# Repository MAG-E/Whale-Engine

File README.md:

# Whale-Engine
CMOS based optical drone synthesiser

Youtube video: https://youtu.be/fdHDt4L-P9A

Everything you need to build one of these is included. This is not a 'true' beginner project, some mechanical and electrical skills are required.
Some assumptions will need to be made with drilling and wiring the output jack and power input jack.
The PCB files are formatted for JLC manufacture. The original PCB was hand etched so the schematic includes jumpers. These can be ignored if you
order a PCB.

The finished device draws 50mA at most, making it suitable for battery or USB power. Do not connect more than 9V, the zener diode regulation is very crude.
The output is not suitable for powering headphones and benefits from being connected to an amplifier. It is designed to be connected to an amplified speaker.

Known issues:
- Even with modulation switches set to off, the modulations oscillators have an effect on the primary oscillator.
  This could be fixed by using a separate 4093 IC for the modulation oscillators. In one unit, I isolated the LEDs with
  a transistor and the issue was still there. 
  The problem is only with a TI CD4093, the now obsolete OnSemi CD4093s I have do not exhibit this.
  This isn't a refined product, it was built for kids christmas presents.
  
MAG-03/01/2022

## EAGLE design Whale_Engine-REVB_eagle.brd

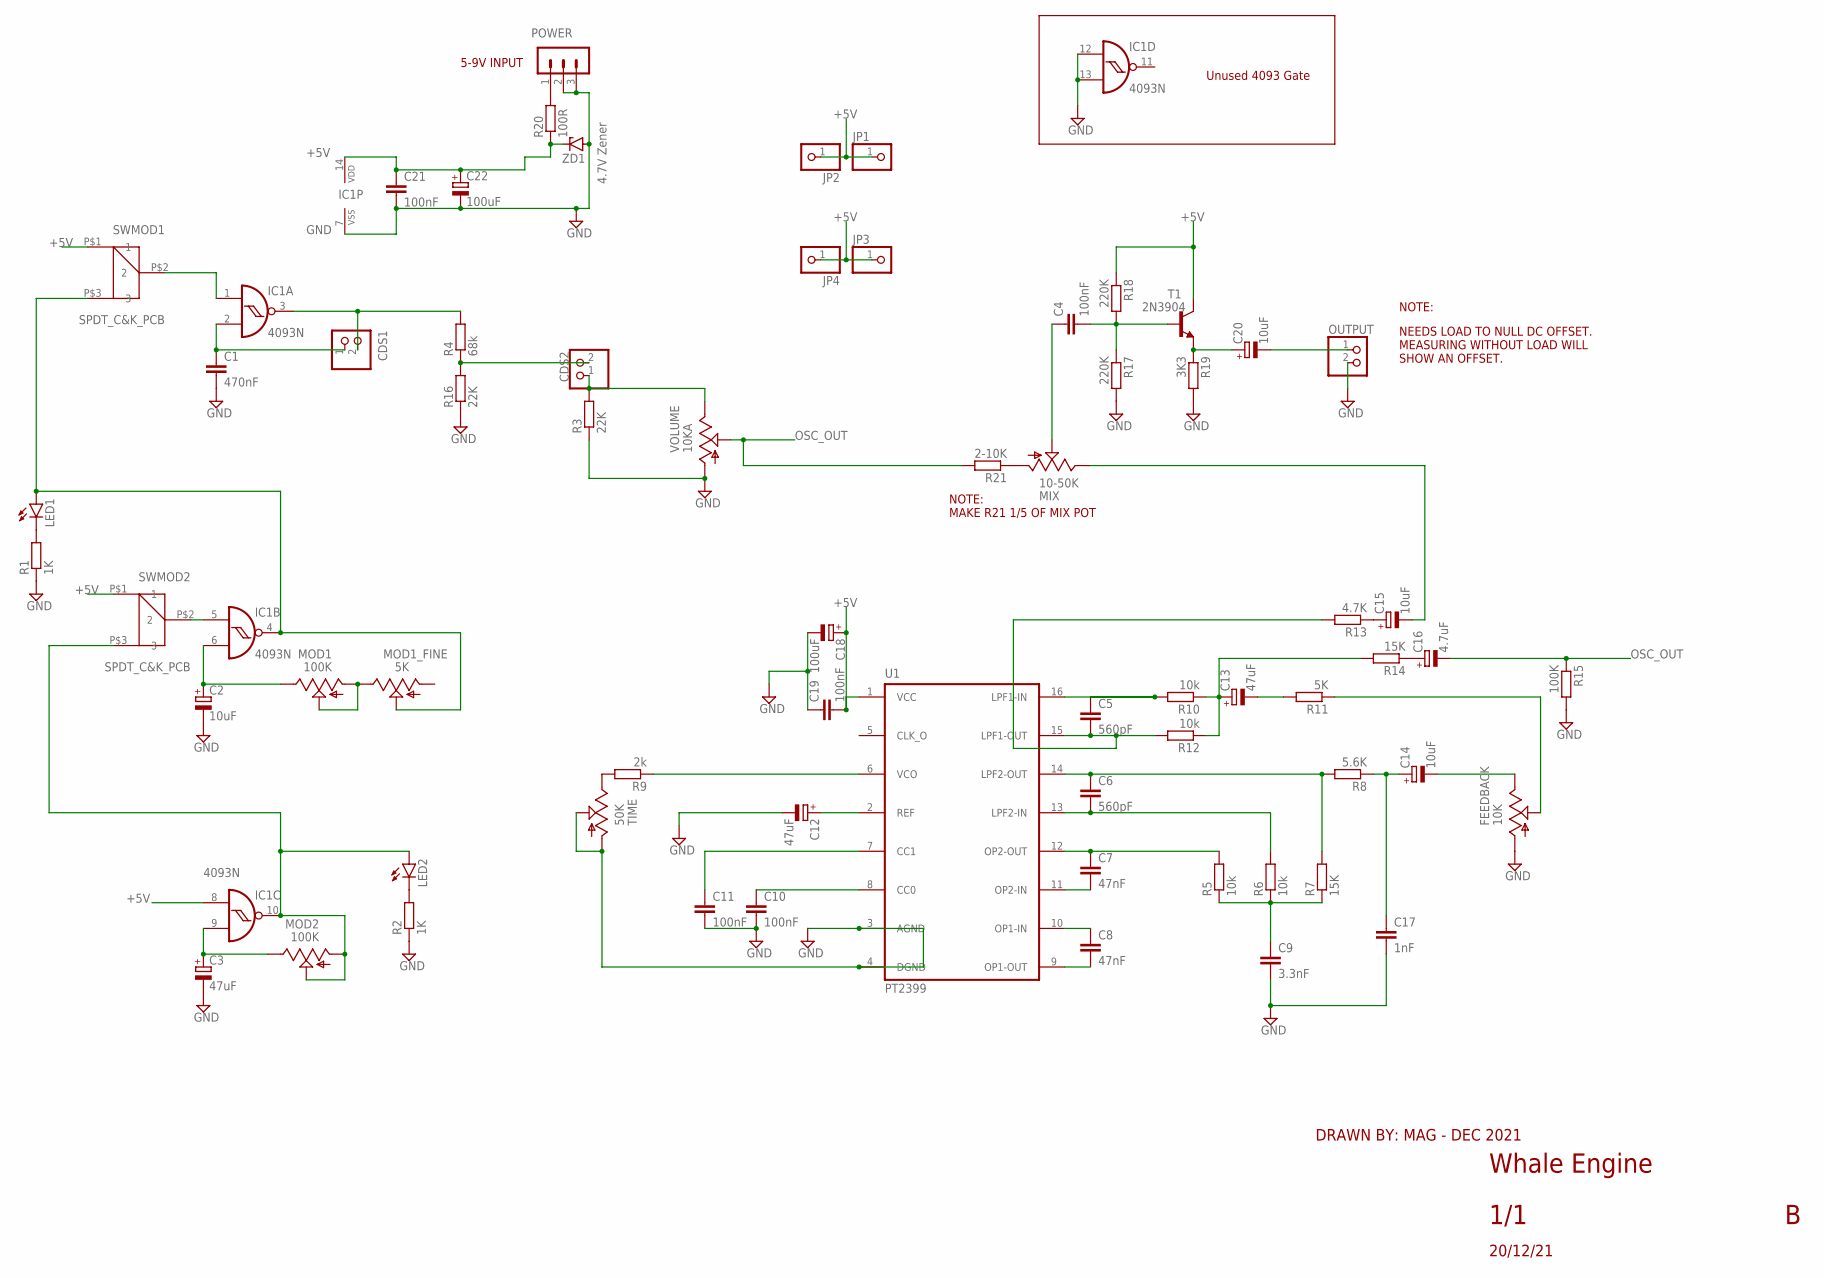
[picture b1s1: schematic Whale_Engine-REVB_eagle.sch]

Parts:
C1: 470nF; C7.5B3
C2, C14, C15, C20: 10uF; E2-5
C3, C12, C13: 47uF; E2-5
C4: 100nF; C050-025X075
C5, C6: 560pF; C2.5-2
C7, C8: 47nF; C2.5-2
C9: 3.3nF; C2.5-2
C10, C11, C19, C21: 100nF; C2.5-2
C16: 4.7uF; E2-5
C17: 1nF; C2.5-2
C18, C22: 100uF; E2-5
CDS1, CDS2: PINHD-1X2; 1X02
FEEDBACK: 10K; 9MM_SNAP-IN_POT
IC1: 4093N; DIL14
JP1, JP2, JP3, JP4: PINHD-1X1; 1X01
LED1, LED2: LED3MM
MIX: 10-50K; 9MM_SNAP-IN_POT
MOD1, MOD2: 100K; 9MM_SNAP-IN_POT
MOD1_FINE: 5K; 9MM_SNAP-IN_POT
OUTPUT: PINHD-1X2; 1X02
POWER: MA03-1
R1, R2: 1K; 0204/7
R3, R16: 22K; 0204/7
R4: 68k; 0204/7
R5, R6, R10, R12: 10k; 0204/7
R7, R14: 15K; 0204/7
R8: 5.6K; 0204/7
R9: 2k; 0204/7
R11: 5K; 0204/7
R13: 4.7K; 0204/7
R15: 100K; 0204/7
R17, R18: 220K; 0204/7
R19: 3K3; 0204/7
R20: 100R; 0204/7
R21: 2-10K; 0204/7
SWMOD1, SWMOD2: SPDT_C&K_PCB; C&K_SPDT_PCB
T1: 2N3904; TO92
TIME: 50K; 9MM_SNAP-IN_POT
U1: PT2399; DIL16
VOLUME: 10KA; 9MM_SNAP-IN_POT
ZD1: 4.7V Zener; SOD81

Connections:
+5V: C18.+, C19.2, C21.1, C22.+, IC1.8 (I0), IC1.14 (VDD), JP1.1, JP2.1, JP3.1, JP4.1, R18.1, R20.1, SWMOD1.P$1 (1), SWMOD2.P$1 (1), T1.1 (C), U1.1 (VCC), ZD1.C
GND: C1.2, C2.-, C3.-, C9.2, C10.2, C11.2, C12.-, C17.2, C18.-, C19.1, C21.2, C22.-, FEEDBACK.1 (A), IC1.7 (VSS), IC1.12 (I0), IC1.13 (I1), OUTPUT.2, POWER.2, POWER.3, R1.1, R2.1, R3.1, R15.2, R16.1, R17.2, R19.2, TIME.1 (A), TIME.2 (S), U1.3 (AGND), U1.4 (DGND), VOLUME.1 (A), ZD1.A
unnamed: IC1.1 (I0), SWMOD1.P$2 (2)
unnamed: IC1.5 (I0), SWMOD2.P$2 (2)
unnamed: C2.+, IC1.6 (I1), MOD1.3 (E)
unnamed: MOD1.1 (A), MOD1.2 (S), MOD1_FINE.3 (E)
unnamed: IC1.4 (O), LED1.A, MOD1_FINE.2 (S), SWMOD1.P$3 (3)
unnamed: IC1.10 (O), LED2.A, MOD2.1 (A), MOD2.2 (S), SWMOD2.P$3 (3)
unnamed: C1.1, CDS1.1, IC1.2 (I1)
unnamed: CDS1.2, IC1.3 (O), R4.2
unnamed: LED1.K (C), R1.2
unnamed: LED2.K (C), R2.2
unnamed: C3.+, IC1.9 (I1), MOD2.3 (E)
unnamed: CDS2.2, R4.1, R16.2
unnamed: CDS2.1, R3.2, VOLUME.3 (E)
unnamed: C5.1, R10.2, U1.16 (LPF1-IN)
unnamed: C5.2, R12.2, R13.2, U1.15 (LPF1-OUT)
unnamed: C6.1, R7.2, R8.2, U1.14 (LPF2-OUT)
unnamed: C6.2, R6.2, U1.13 (LPF2-IN)
unnamed: C7.1, R5.2, U1.12 (OP2-OUT)
unnamed: C7.2, U1.11 (OP2-IN)
unnamed: C8.1, U1.10 (OP1-IN)
unnamed: C8.2, U1.9 (OP1-OUT)
unnamed: C9.1, R5.1, R6.1, R7.1
unnamed: C10.1, U1.8 (CC0)
unnamed: C11.1, U1.7 (CC1)
unnamed: R9.1, U1.6 (VCO)
unnamed: R9.2, TIME.3 (E)
unnamed: C4.2, R17.1, R18.2, T1.2 (B)
unnamed: C12.+, U1.2 (REF)
unnamed: C13.+, R10.1, R12.1, R14.2
unnamed: C13.-, R11.2
unnamed: FEEDBACK.2 (S), R11.1
unnamed: C14.-, FEEDBACK.3 (E)
unnamed: C14.+, C17.1, R8.1
unnamed: C15.+, R13.1
unnamed: C4.1, MIX.2 (S)
unnamed: C16.+, R14.1
unnamed: C20.+, R19.1, T1.3 (E)
unnamed: C20.-, OUTPUT.1
unnamed: C15.-, MIX.3 (E)
unnamed: MIX.1 (A), R21.1
unnamed: POWER.1, R20.2
OSC_OUT: C16.-, R15.1, R21.2, VOLUME.2 (S)

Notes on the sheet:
5-9V INPUT
NOTE:
NEEDS LOAD TO NULL DC OFFSET. MEASURING WITHOUT LOAD WILL SHOW AN OFFSET.
Whale Engine
1/1
20/12/21
DRAWN BY: MAG - DEC 2021
NOTE: MAKE R21 1/5 OF MIX POT
Unused 4093 Gate

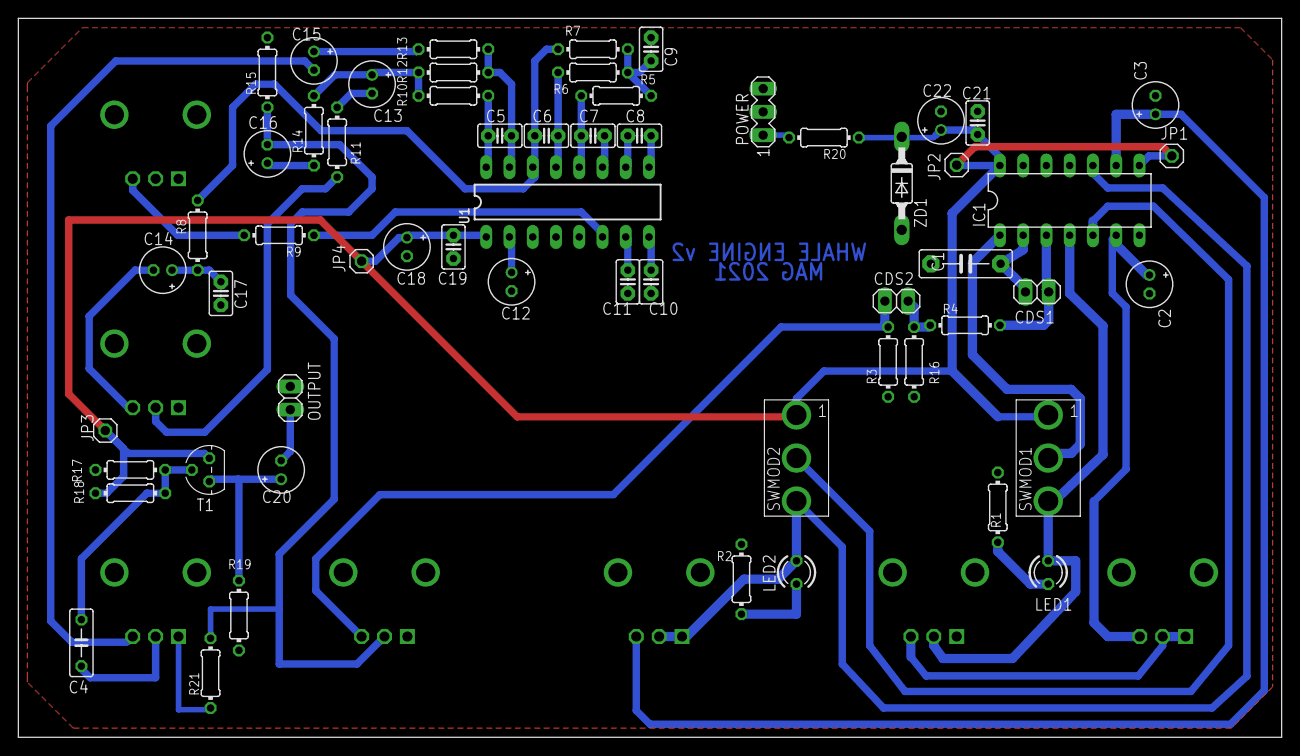
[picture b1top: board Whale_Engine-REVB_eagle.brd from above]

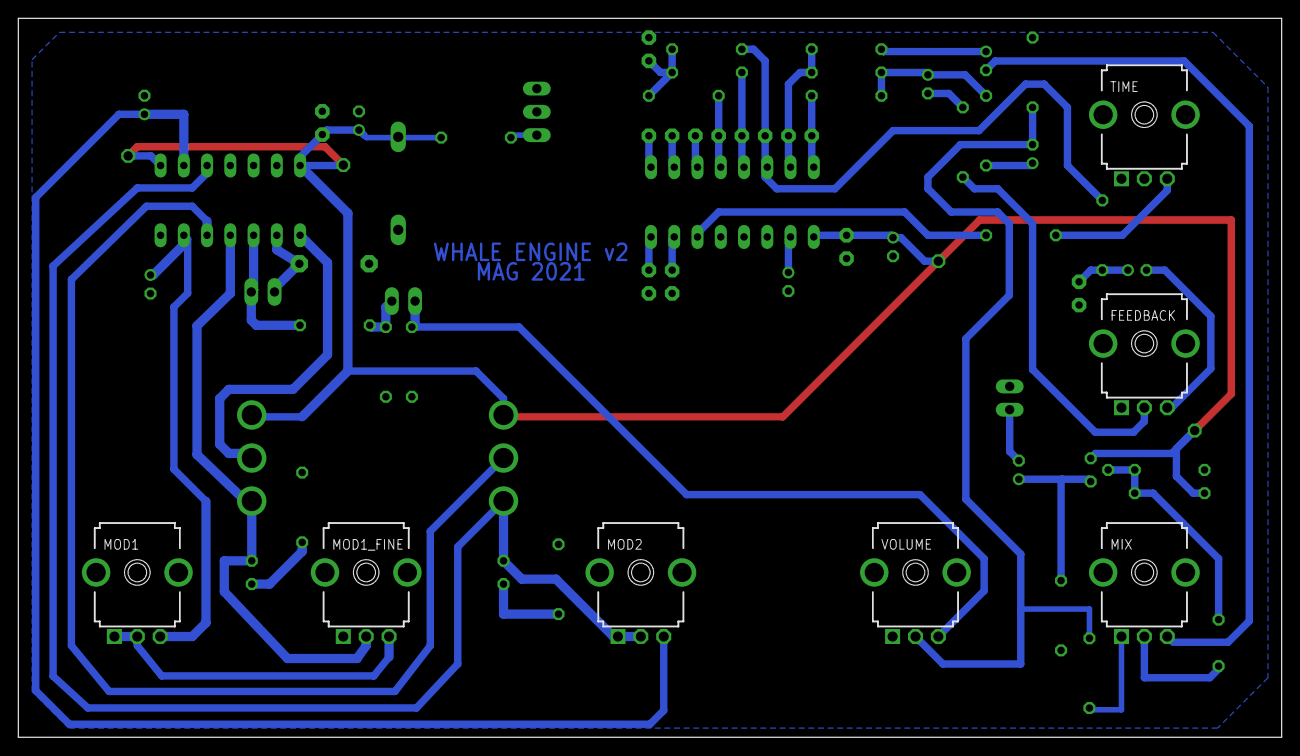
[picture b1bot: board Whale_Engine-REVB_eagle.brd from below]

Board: 2 copper layers, 138.0 x 78.5 mm, 66 parts (7 on the bottom side), 44 nets.

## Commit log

2022-01-03 Create EAGLE

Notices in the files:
parts and their libraries:
princeton-tech: Copyright (C) 2010, Bob Starr
